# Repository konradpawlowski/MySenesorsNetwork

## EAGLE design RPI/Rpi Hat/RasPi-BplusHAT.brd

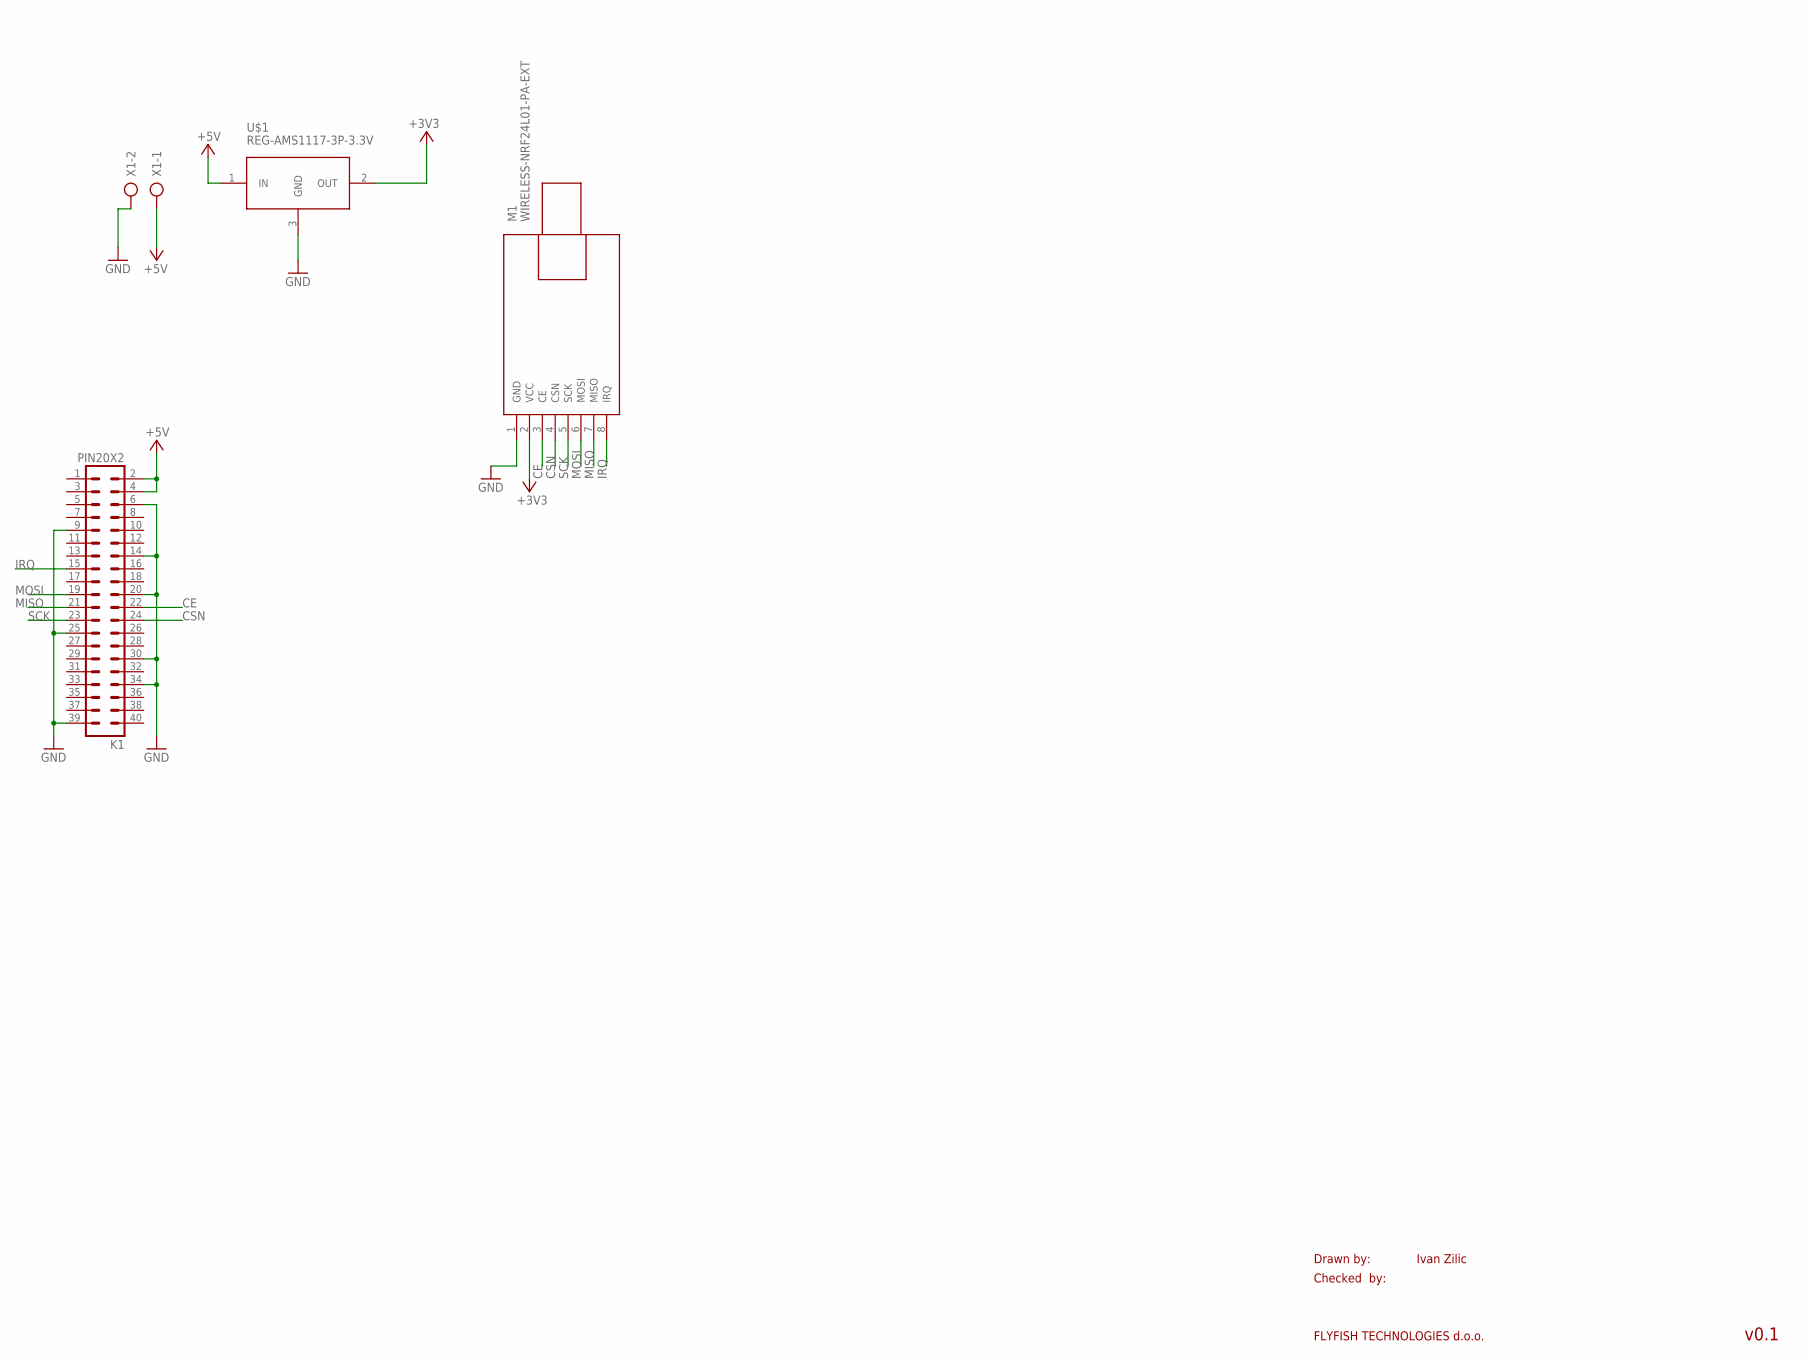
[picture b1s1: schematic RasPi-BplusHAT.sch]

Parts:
K1: PIN20X2; PIN_20X2
M1: WIRELESS-NRF24L01-PA-EXT
U$1: REG-AMS1117-3P-3.3V; REG-AMS1117-3P
X1: AK500/2

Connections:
+3V3: M1.2 (VCC), U$1.2 (OUT)
+5V: K1.2, K1.4, U$1.1 (IN), X1.1
CE: K1.22, M1.3 (CE)
CSN: K1.24, M1.4 (CSN)
GND: K1.6, K1.9, K1.14, K1.20, K1.25, K1.30, K1.34, K1.39, M1.1 (GND), U$1.3 (GND), X1.2
IRQ: K1.15, M1.8 (IRQ)
MISO: K1.21, M1.7 (MISO)
MOSI: K1.19, M1.6 (MOSI)
SCK: K1.23, M1.5 (SCK)

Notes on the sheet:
Drawn by:
Checked by:
FLYFISH TECHNOLOGIES d.o.o.
Ivan Zilic
v0.1

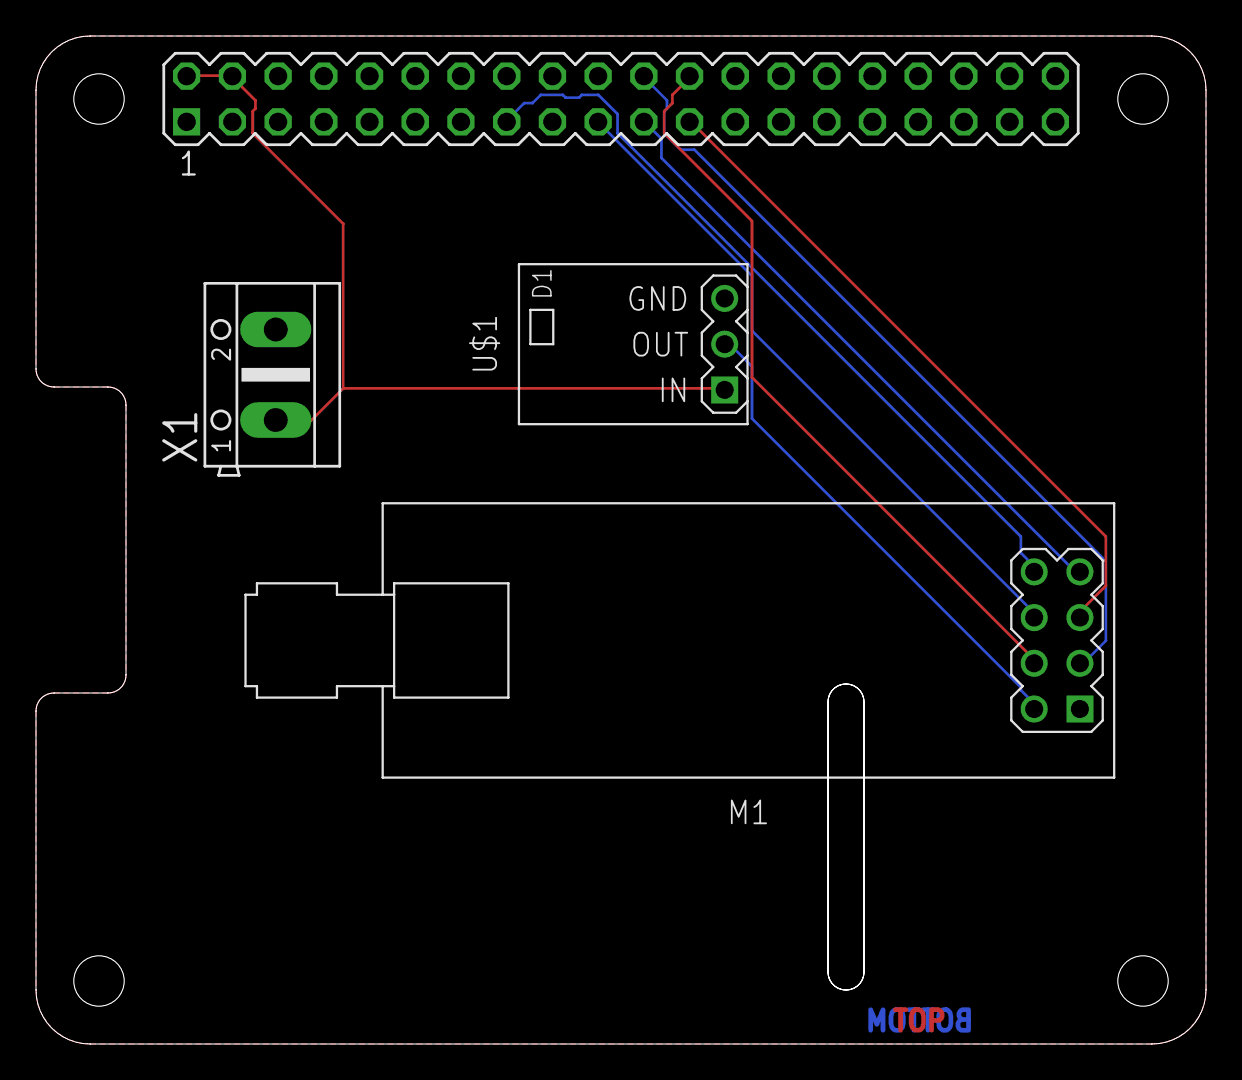
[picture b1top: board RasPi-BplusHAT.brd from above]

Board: 2 copper layers, 65.0 x 56.0 mm, 4 parts (0 on the bottom side), 9 nets.

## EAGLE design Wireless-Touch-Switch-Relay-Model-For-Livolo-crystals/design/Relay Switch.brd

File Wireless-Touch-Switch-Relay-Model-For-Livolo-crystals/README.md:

**The project is in development. You can see the status of this and other nodes from [my work panel](https://trello.com/b/6nWJ42Qx/smarthome) (In Spanish)**

### English  (Google Translate): 
-----------------------------------------------------

This circuit is a touch switch that replaces the wall switches and allows you to control the lighting (on and off, in the future I want to make another plate to regulate the brightness), uses two PCBs, the first one is black and includes the microcontroller, antenna, etc., the second PCB is red and includes the AC part, power supply, relays, etc.

**Features:**
- ATmega328P 3.3V 8Mhz microcontroller, with pads for external oscillator (optional)
- Antenna NRF24L01 SMD
- Touch push button TTP223 + HTTM light reflector to interact with the switch manually.
- RGB LED (The color blue does not have PWM) to indicate the status of the relays or RF connection.
- Flash chip for FOTA
- Chip ATSHA204A for signature.
- JST-8-1MM AVRISP + UART programming connector (UART requires 100nF capacitor in the cable)
- 2 relays of HF46F-5-HS1 of 5A to control AC load
- DS18B20 sensor near the power supply to control the internal temperature.
- Power supply HILINK HLK-PM01 5V
- Voltage regulator AMS1117-3.3

**Requirements:**
- It is necessary to connect the Neutral cable to the power supply. 
- It is necessary to print two pieces of plastic with a 3D printer to house the circuits, hold the glass and be able to screw the switch to the wall.

** Project status (OK / PENDING TO TEST / ERROR): **
- ATmega328P _OK_
- NRF24L01 _OK_
- RGB LED _OK_
- ISP Flash FOTA _OK_
- ATSHA204A _PENDING_
- Connector AVRISP + UART _OK_
- Reles _OK_
- DS18B20 _OK_
- HILINK HLK-PM01 5V _OK_
- AMS1117-3.3 _OK_

**Notes:**
- The data of the BOM tab may be obsolete.

### Spanish:
-----------------------------------------------------

Este circuito se trata de un interruptor táctil que sustituye los interruptores de pared y que permite controlar la iluminación (encendido y apagado, en el futuro quiero hacer otra placa para regular el brillo), utiliza dos PCB, el primero es de color negro e incluye el microcontrolador, antena, etc., el segundo PCB es de color rojo e incluye la parte AC, fuente de alimentación, relés, etc.

**Características:**
- Microcontrolador ATmega328P 3.3V 8Mhz, con pads para oscilador externo (opcional)
- Antena NRF24L01 SMD
- Pulsador táctil TTP223 + reflector de luz HTTM para interactuar con el interruptor manualmente.
- Led RGB (El color azul no tiene PWM) para indicar el estado de los relés o conexión RF.
- Chip flash para FOTA
- Chip ATSHA204A para firma.
- Conector de programación JST-8-1MM AVRISP+UART (UART requiere condensador de 100nF en el cable)
- 2 relés de HF46F-5-HS1 de 5A para controlar la carga AC
- Sensor DS18B20 cerca de la fuente de alimentación para controlar la temperatura interna.
- Fuente de alimentación HILINK HLK-PM01 5V
- Regulador de tensión AMS1117-3.3

**Requisitos:**
- Es necesario conectar el cable de Neutro para la fuente de alimentación.
- Es necesario imprimir dos piezas de plástico con una impresora 3D para albergar los circuitos, sujetar el cristal y poder atornillar el interruptor a la pared.

**Estado del proyecto (OK / PENDIENTE DE PROBAR / ERRORES):**
- ATmega328P _OK_
- NRF24L01 _OK_
- LED RGB _OK_
- ISP Flash FOTA _OK_
- ATSHA204A _PENDIENTE_
- Connector AVRISP+UART _OK_
- Reles _OK_
- DS18B20 _OK_
- HILINK HLK-PM01 5V _OK_
- AMS1117-3.3 _OK_

**Notas:**
- Los datos de la pestaña BOM pueden estar obsoletos.

### Changelog
-----------------------------------------------------

**2018/XX**

    + TOUCH SWITCH BOARD V2.2:
        - Improve logos and change position.

    + RELAY SWITCH BOARD V1.2:
        - Change AC connectors by ones at an angle (and modify the plastic shell with the new design)

**2017/12**

    + TOUCH SWITCH BOARD V2.1:
        - Move programming connector to the inside of the board, it was colliding with the plastic housing.
        - Modify the pinout of the RGB LED, the green and blue colors of the reverse.
        - Add text that identifies the functionality of the board.

    + RELAY SWITCH BOARD V1.1:
        - Replace SSR relay with 5A mechanical relays.
        - Add text that identifies the functionality of the board.

**2017/10 INITIAL VERSION**

    + TOUCH SWITCH BOARD V2.0.
    + RELAY SWITCH BOARD V1.0.

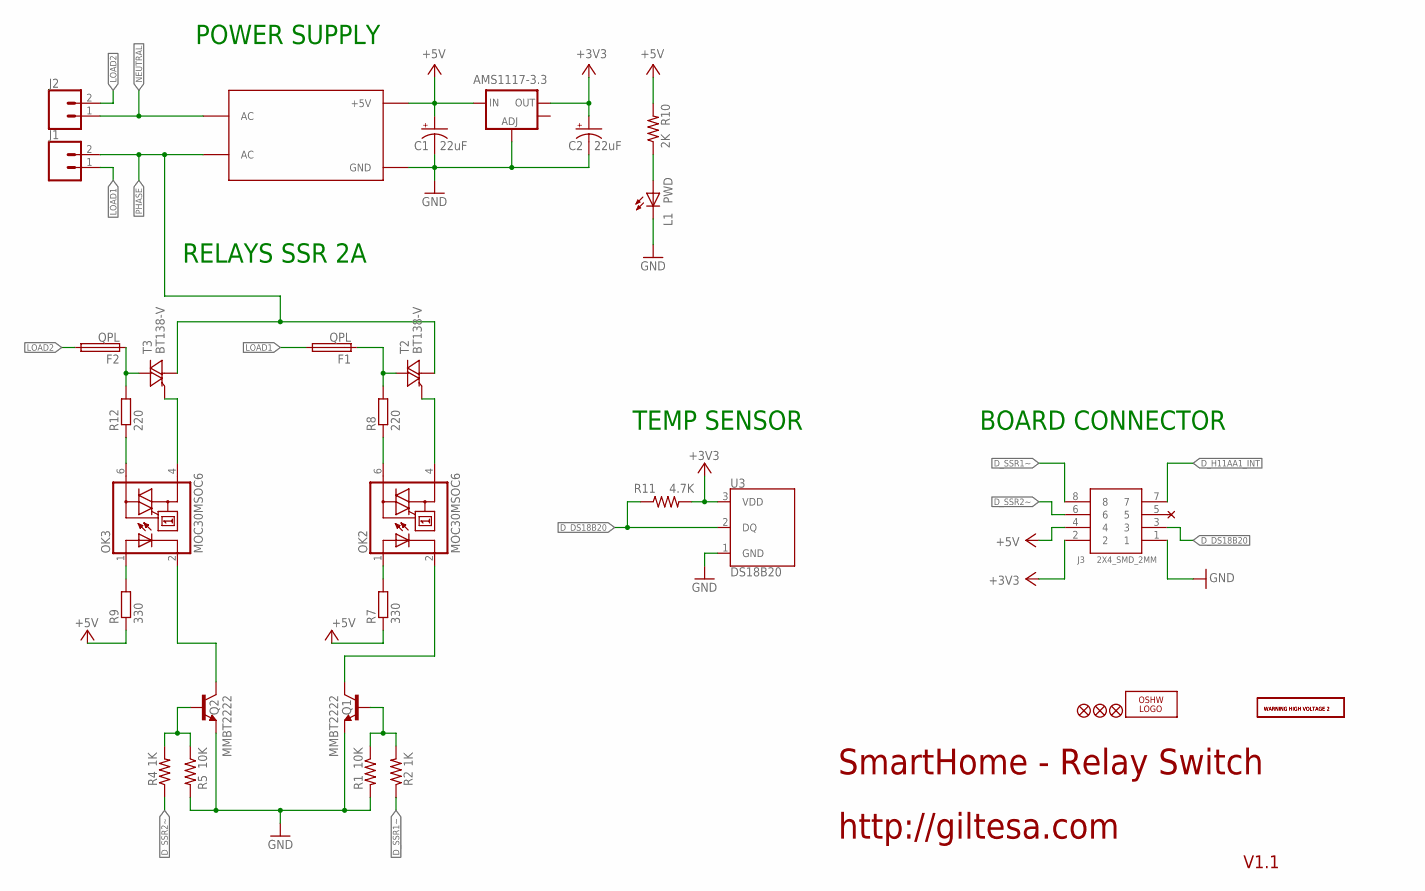
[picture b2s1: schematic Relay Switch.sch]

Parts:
AMS1117-3.3: V_REG_LM1117SOT223; SOT223
C1, C2: 22uF; EIA3528
F1, F2: QPL; TE5
J1, J2: TERMINAL_5MM_2P
J3: 2X4_SMD_2MM; 2X4_SMD_2.0MM
L1: PWD; CHIP-LED0805
LOGO1: OSHW_LOGO_FILLX0150-NT; OSHW_FILLX150_NOTEXT
OK2, OK3: MOC30MSOC6; DIL6-SMD
Q1, Q2: MMBT2222; SOT23
R1, R5: 10K; R0603
R2, R4: 1K; R0603
R7, R9: 330; M0805
R8, R12: 220; M0805
R10: 2K; R0603
R11: 4.7K; R0603
T2, T3: BT138-V; TO220BV
U3: DS18B20
U$1: HILINK_HLK-PM01_5V
U$3, U$4: WARNING_HIGH_VOLTAGE_2
U$6, U$7, U$14: FIDUCIAL1X2; FIDUCIAL-1X2

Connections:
+3V3: AMS1117-3.3.2 (OUT), C2.A (+), J3.2, R11.2, U3.3 (VDD)
+5V: AMS1117-3.3.3 (IN), C1.A (+), J3.4, R7.1, R9.1, R10.2, U$1.+5V
D_DS18B20: J3.3, R11.1, U3.2 (DQ)
D_H11AA1_INT: J3.7
D_SSR1~: J3.8, R2.1
D_SSR2~: J3.6, R4.1
GND: AMS1117-3.3.1 (ADJ), C1.C (-), C2.C (-), J3.1, L1.C, Q1.2 (E), Q2.2 (E), R1.2, R5.2, U3.1 (GND), U$1.GND
LOAD1: F1.2, J1.1
LOAD1_1: F1.1, R8.2, T2.T2 (A2)
LOAD2: F2.2, J2.2
LOAD2_1: F2.1, R12.2, T3.T2 (A2)
unnamed: Q1.1 (B), R1.1, R2.2
unnamed: OK2.2 (C), Q1.3 (C)
unnamed: OK2.1 (A), R7.2
unnamed: OK2.6 (A2), R8.1
unnamed: L1.A, R10.1
unnamed: OK2.4 (A1), T2.G
unnamed: OK3.1 (A), R9.2
unnamed: OK3.6 (A2), R12.1
unnamed: OK3.4 (A1), T3.G
unnamed: Q2.1 (B), R4.2, R5.1
unnamed: OK3.2 (C), Q2.3 (C)
NEUTRAL: J2.1, U$1.AC@2 (AC)
PHASE: J1.2, T2.T1 (A1), T3.T1 (A1), U$1.AC@1 (AC)

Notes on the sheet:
POWER SUPPLY
SmartHome - Relay Switch
http://giltesa.com
V1.1
RELAYS SSR 2A
TEMP SENSOR
BOARD CONNECTOR

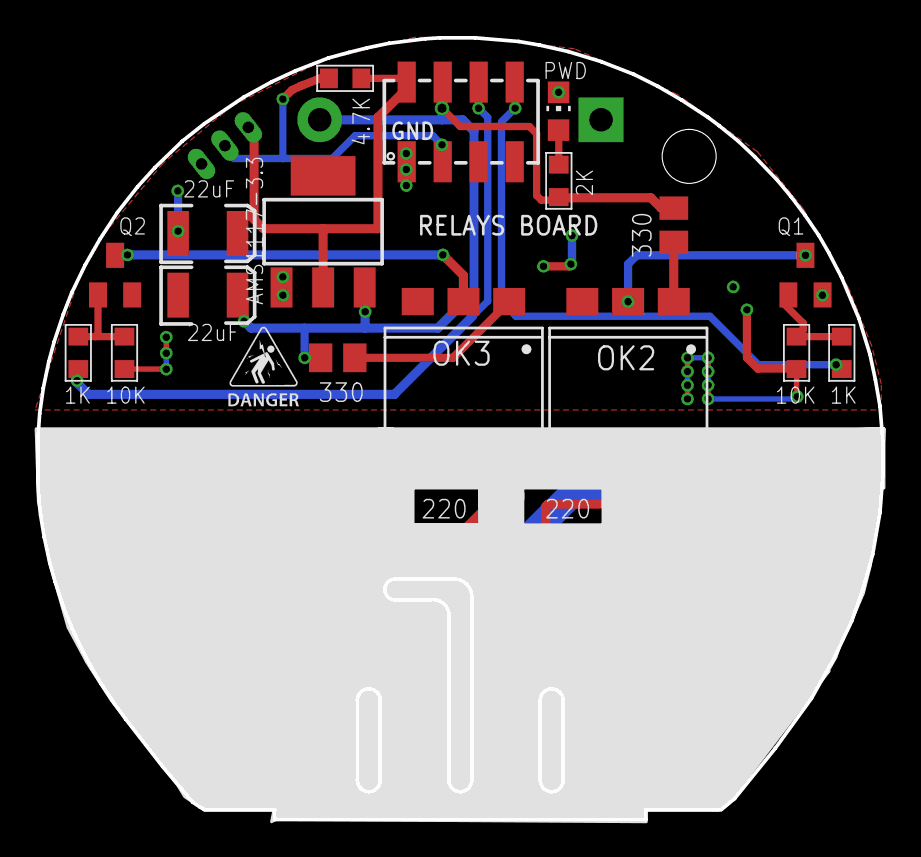
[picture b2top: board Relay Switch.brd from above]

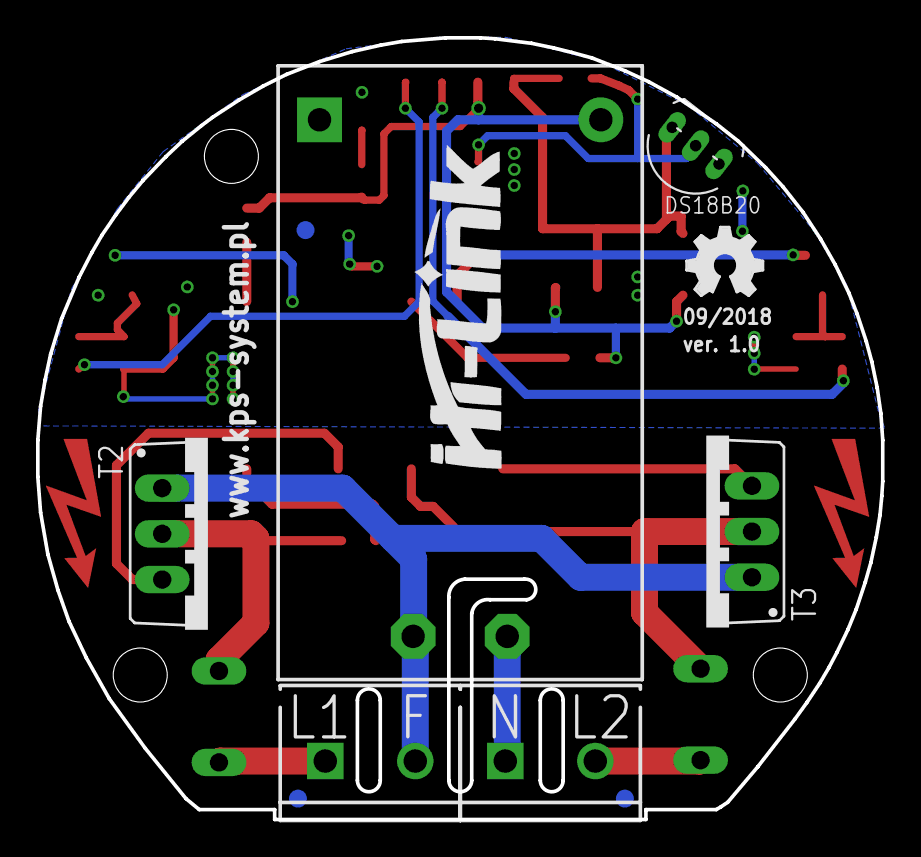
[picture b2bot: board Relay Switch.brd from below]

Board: 2 copper layers, 46.9 x 43.4 mm, 34 parts (10 on the bottom side), 23 nets.

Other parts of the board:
U$2: ELECTROCUTION_SMALL

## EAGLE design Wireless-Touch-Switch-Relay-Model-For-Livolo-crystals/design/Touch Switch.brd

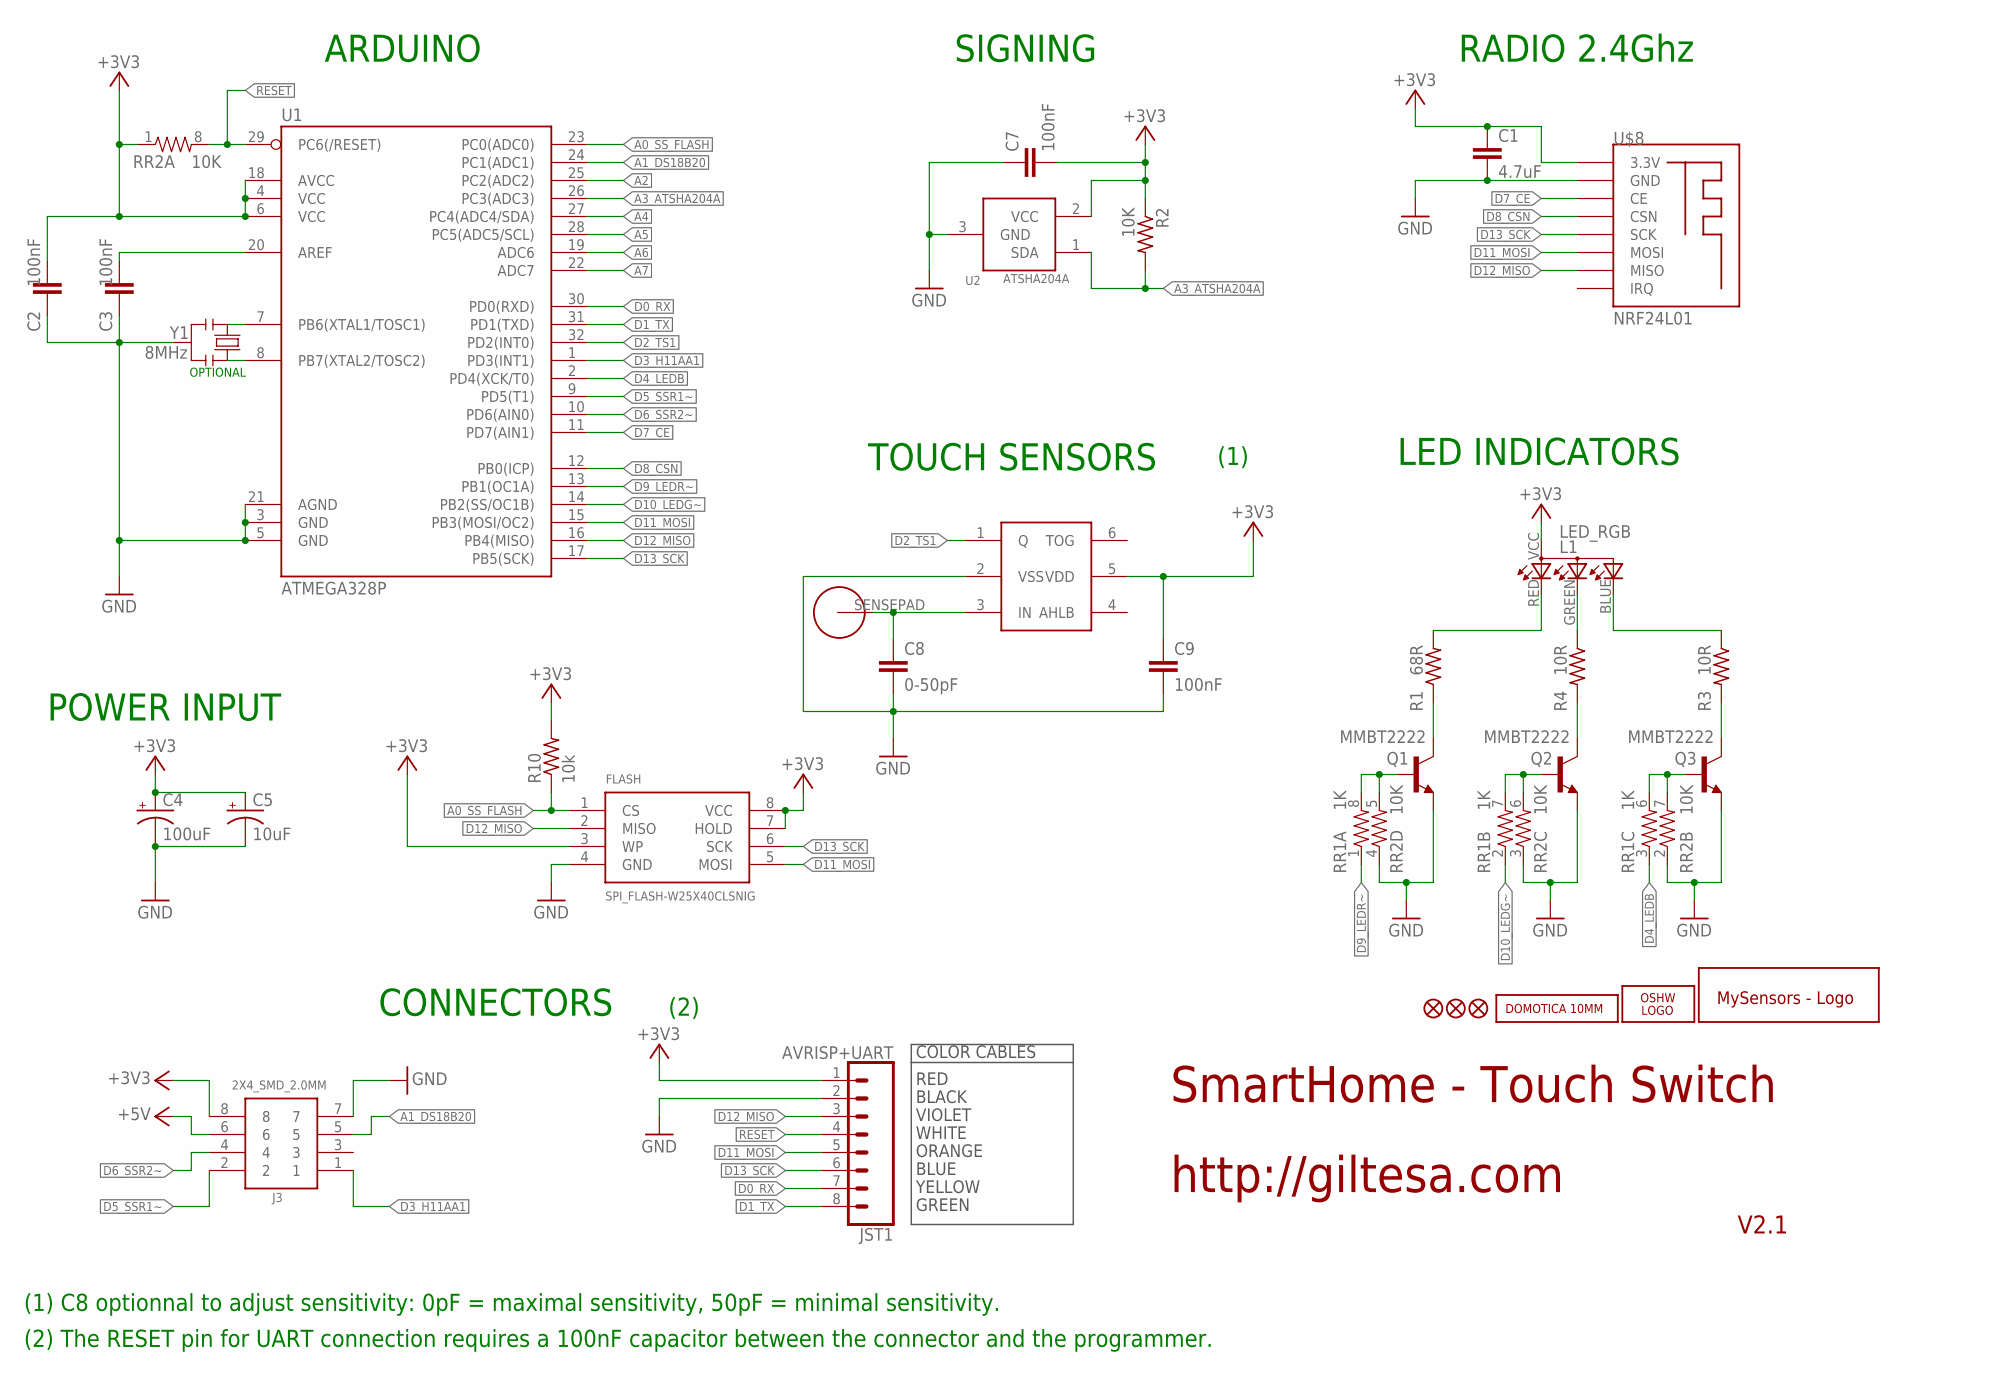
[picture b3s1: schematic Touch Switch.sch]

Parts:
C1: 4.7uF; C1206
C2, C3, C7, C9: 100nF; C0603
C4: 100uF; EIA3216
C5: 10uF; EIA3216
C8: 0-50pF; C0603
FLASH: SPI_FLASH-W25X40CLSNIG; SO08
J3: 2X4_SMD_2.0MM
JST1: AVRISP+UART; JST-8-1MM-SMD
L1: LED_RGB; LED_RGB_1206_SIDE
LOGO1: OSHW_LOGO_FILLX0150-NT; OSHW_FILLX150_NOTEXT
Q1, Q2, Q3: MMBT2222; SOT23
R1: 68R; R0603
R2: 10K; R0603
R3, R4: 10R; R0603
R10: 10k; R0603
RR1: 1K; 0603-ARV
RR2: 10K; 0603-ARV
TTP1: TTP223; SOT-23-6
U1: ATMEGA328P; TQFP32-08
U2: ATSHA204A; SOT23-3
U$1: HTTM_SENSEPAD
U$2: MYSENSORS
U$5: DOMOTICA-10MM
U$6, U$7, U$14: FIDUCIAL1X2; FIDUCIAL-1X2
U$8: NRF24L01; NRF24L01_SMD
Y1: 8MHz; RESONATOR

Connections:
+3V3: C1.1, C2.2, C4.A (+), C5.A (+), C7.2, C9.1, FLASH.3 (WP), FLASH.7 (HOLD), FLASH.8 (VCC), J3.8, JST1.1, L1.VCC, R2.1, R10.2, RR2.1, TTP1.5 (VDD), U1.4 (VCC), U1.6 (VCC), U1.18 (AVCC), U2.2 (VCC), U$8.3.3V
+5V: J3.6
A0_SS_FLASH: FLASH.1 (CS), R10.1, U1.23 (PC0(ADC0))
A1_DS18B20: J3.5, U1.24 (PC1(ADC1))
A2: U1.25 (PC2(ADC2))
A3_ATSHA204A: R2.2, U1.26 (PC3(ADC3)), U2.1 (SDA)
A4: U1.27 (PC4(ADC4/SDA))
A5: U1.28 (PC5(ADC5/SCL))
A6: U1.19 (ADC6)
A7: U1.22 (ADC7)
D0_RX: JST1.7, U1.30 (PD0(RXD))
D1_TX: JST1.8, U1.31 (PD1(TXD))
D2_TS1: TTP1.1 (Q), U1.32 (PD2(INT0))
D3_H11AA1: J3.1, U1.1 (PD3(INT1))
D4_LEDB: RR1.3 (1), U1.2 (PD4(XCK/T0))
D5_SSR1~: J3.2, U1.9 (PD5(T1))
D6_SSR2~: J3.4, U1.10 (PD6(AIN0))
D7_CE: U1.11 (PD7(AIN1)), U$8.CE
D8_CSN: U1.12 (PB0(ICP)), U$8.CSN
D9_LEDR~: RR1.1, U1.13 (PB1(OC1A))
D10_LEDG~: RR1.2 (1), U1.14 (PB2(SS/OC1B))
D11_MOSI: FLASH.5 (MOSI), JST1.5, U1.15 (PB3(MOSI/OC2)), U$8.MOSI
D12_MISO: FLASH.2 (MISO), JST1.3, U1.16 (PB4(MISO)), U$8.MISO
D13_SCK: FLASH.6 (SCK), JST1.6, U1.17 (PB5(SCK)), U$8.SCK
GND: C1.2, C2.1, C3.1, C4.C (-), C5.C (-), C7.1, C8.2, C9.2, FLASH.4 (GND), J3.7, JST1.2, Q1.2 (E), Q2.2 (E), Q3.2 (E), RR2.2 (1), RR2.3 (1), RR2.4 (1), TTP1.2 (VSS), U1.3 (GND), U1.5 (GND), U1.21 (AGND), U2.3 (GND), U$8.GND, Y1.2
unnamed: Q1.3 (C), R1.1
unnamed: L1.GREEN, R4.1
unnamed: L1.RED, R1.2
unnamed: Q2.1 (B), RR1.7 (2), RR2.6 (2)
unnamed: Q1.1 (B), RR1.8 (2), RR2.5 (2)
unnamed: Q2.3 (C), R4.2
unnamed: Q3.3 (C), R3.2
unnamed: Q3.1 (B), RR1.6 (2), RR2.7 (2)
unnamed: C8.1, TTP1.3 (IN), U$1.SENSEPAD
unnamed: L1.BLUE, R3.1
unnamed: U1.7 (PB6(XTAL1/TOSC1)), Y1.1
unnamed: U1.8 (PB7(XTAL2/TOSC2)), Y1.3
unnamed: C3.2, U1.20 (AREF)
RESET: JST1.4, RR2.8 (2), U1.29 (PC6(/RESET))

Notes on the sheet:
POWER INPUT
TOUCH SENSORS
(1) C8 optionnal to adjust sensitivity: 0pF = maximal sensitivity, 50pF = minimal sensitivity.
LED INDICATORS
CONNECTORS
RADIO 2.4Ghz
SIGNING
OPTIONAL
ARDUINO
(1)
SmartHome - Touch Switch
http://giltesa.com
V2.1
RED
BLACK
VIOLET
WHITE
ORANGE
BLUE
YELLOW
GREEN
COLOR CABLES
(2)
(2) The RESET pin for UART connection requires a 100nF capacitor between the connector and the programmer.

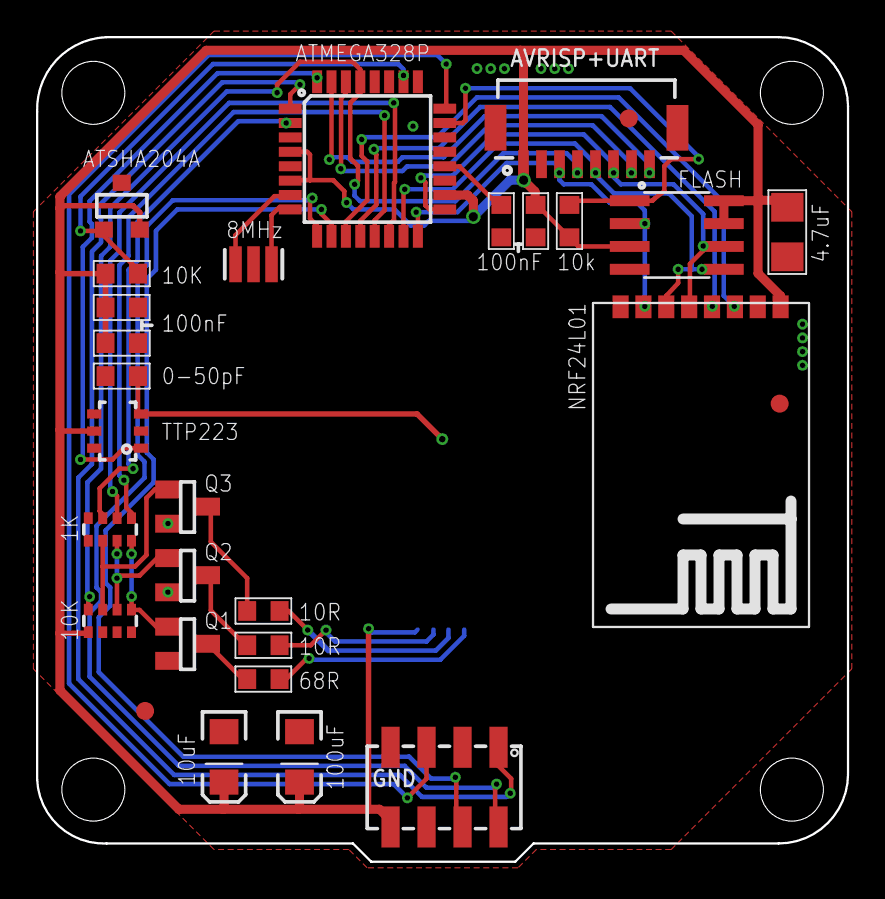
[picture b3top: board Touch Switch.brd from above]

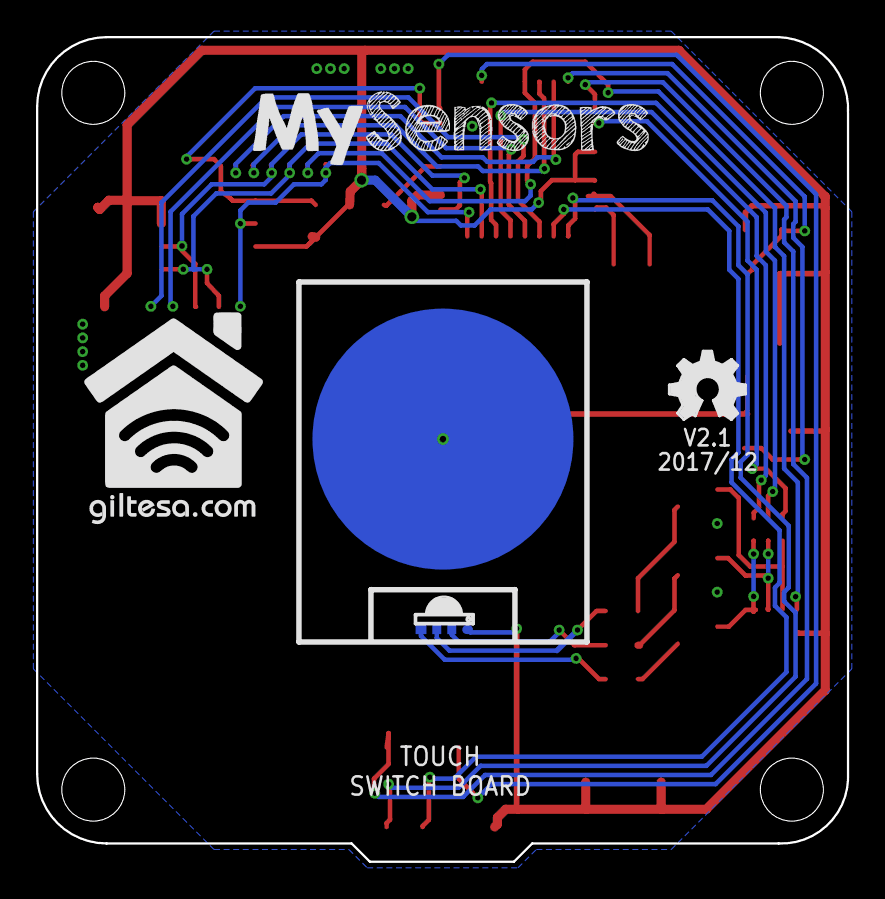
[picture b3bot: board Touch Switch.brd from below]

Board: 2 copper layers, 45.0 x 45.8 mm, 34 parts (5 on the bottom side), 33 nets.

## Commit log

2018-03-09 Add .gitignore and .gitattributes.
2018-03-09 Add project files.
2018-03-13 bez dht
2018-03-29 Zmiany
2018-04-12 serial rf
2018-05-11 roomController
2019-03-30 Oprogramowanie do włacznika na baterie i odbirnika dla asi
2019-04-08 rtemote relay
2019-07-02 Outside sensors
2019-09-18 outside sensor
2019-10-04 add temps
2019-11-17 roomCOntroller update
2019-11-19 Aktulizacja sensorów
2019-12-28 ZMiany Remote v2
2020-01-13 remote relay 2 working
2020-01-25 modify catalog
2020-01-25 garage controller
2020-01-26 ostatnie szlify
2020-03-04 remote relay 2 update

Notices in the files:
parts and their libraries:
diy-modules: Released under the Creative Commons Attribution 4.0 International License: http://creativecommons.org/licenses/by/4.0
SparkFun-DigitalIC: Licensing: Creative Commons ShareAlike 4.0 International - https://creativecommons.org/licenses/by-sa/4.0
